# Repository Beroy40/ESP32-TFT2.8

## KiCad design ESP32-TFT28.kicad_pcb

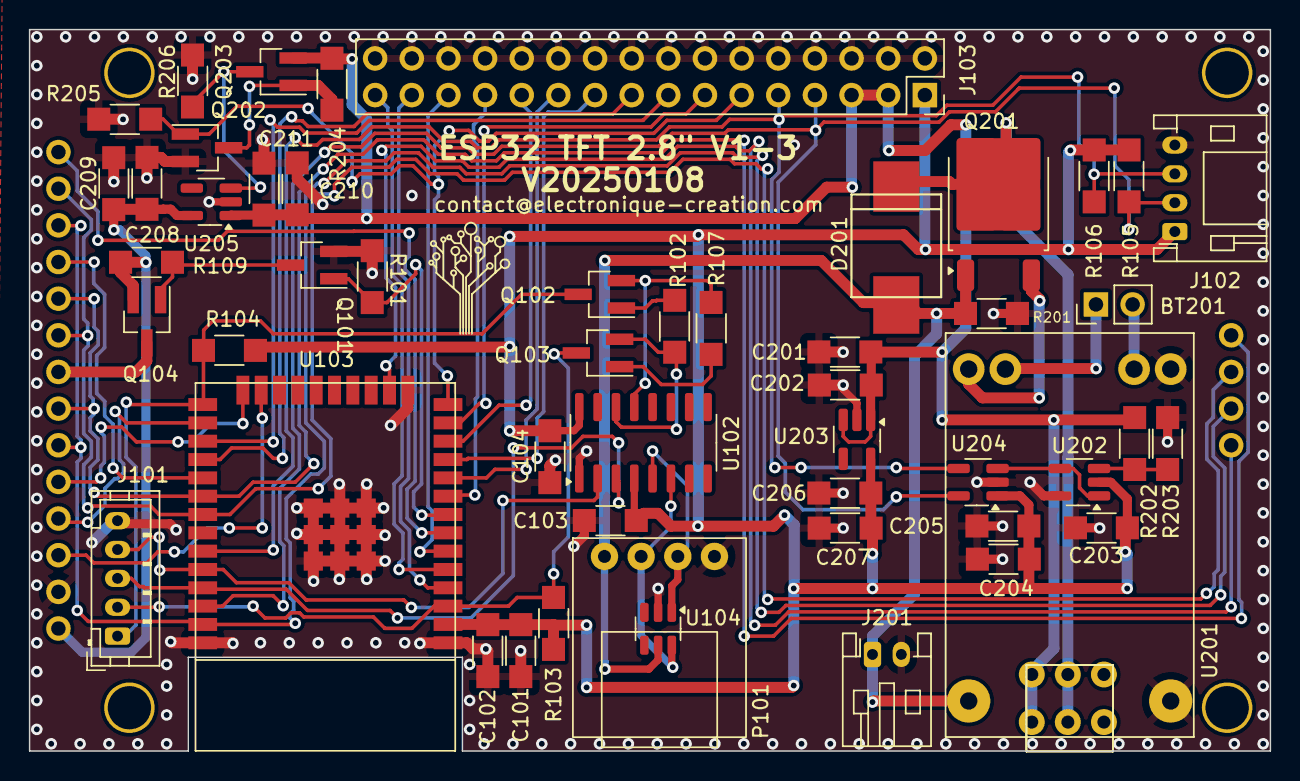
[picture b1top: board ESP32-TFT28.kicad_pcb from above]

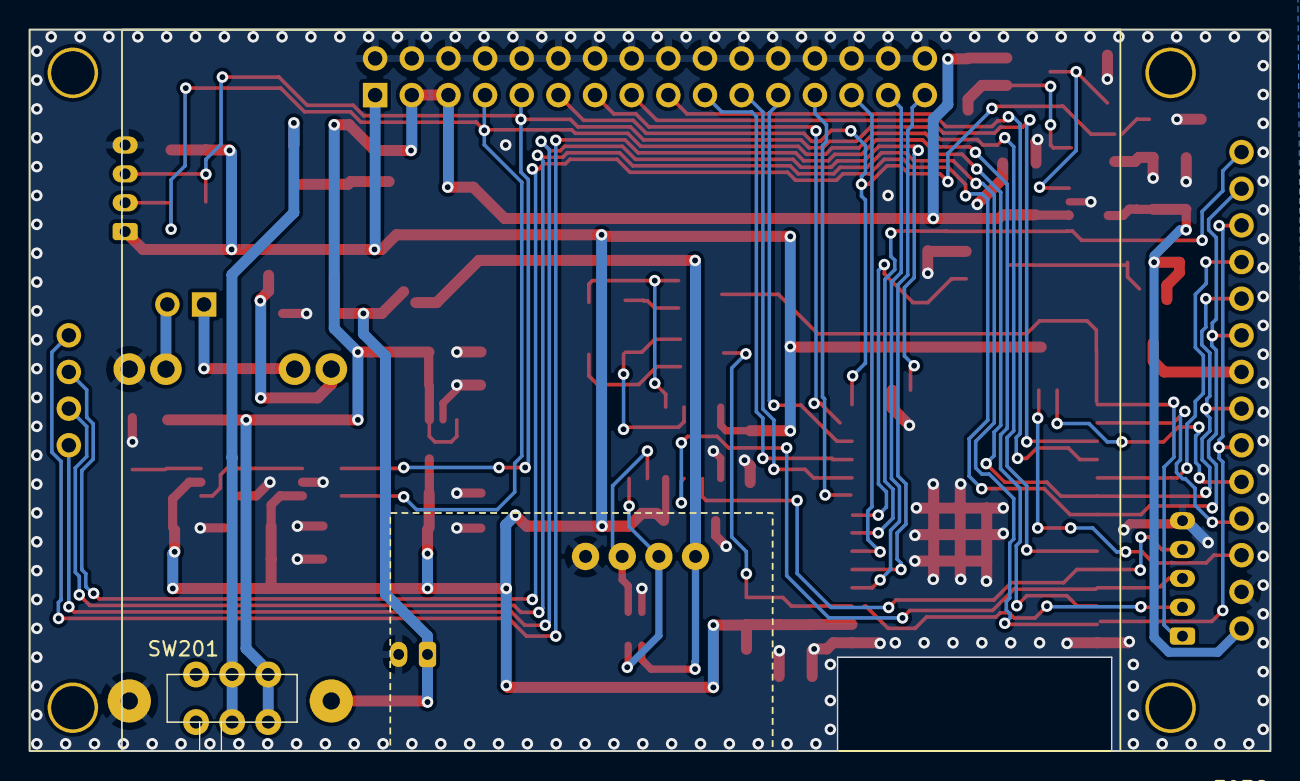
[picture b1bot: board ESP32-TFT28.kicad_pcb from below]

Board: 2 copper layers, 86.0 x 50.0 mm, 54 parts (2 on the bottom side), 48 nets.

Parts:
BT201: Battery_Cell; PinHeader_1x02_P2.54mm_Vertical
C101: CC1206KKX7R7BB106; CMS_1206
C102, C103, C104, C202, C203, C205, C207, C209, C211: 100nF; CMS_1206
C201, C204, C206, C208, C210: 10UF; CMS_1206
D201: SS34; DO-214AB_HANDSOLDERING
J101: B5B-PH-K-S(LF)(SN); JST_PH_B5B-PH-K_1x05_P2.00mm_Vertical
J102: Conn_01x04; JST_PH_S4B-PH-K_1x04_P2.00mm_Horizontal
J103: Conn_02x16_Odd_Even; PinSocket_2x16_P2.54mm_Vertical
J201: CONN_01X02; JST_PH_S2B-PH-K_1x02_P2.00mm_Horizontal
L101: LOGO; PetitLogo
P101: USB_C_Module
Q101, Q202: BSS138; SOT-23_Handsoldering
Q102, Q103: MMBT2222ALT1G; SOT-23_Handsoldering
Q104: Q_PMOS_GSD; SOT-23_Handsoldering
Q201: xxxx; TO-252-2
Q203: DPM1045U; SOT-23_Handsoldering
R101, R103, R104, R109, R201, R204, R205, R206: 10k; CMS_1206
R102, R107: 12k; CMS_1206
R105, R106: 4k7; CMS_1206
R202, R203: R; CMS_1206
SW201: JS202011AQN
U101: TFT_28
U102: CH340C; SOIC-16_3.9x9.9mm_P1.27mm
U103: ESP32_WROOM; ESP32-WROOM-JLCPCB
U104: SRV05-4; SOT-23-6
U201: MODULE_CHARGER_LIPO_WITH_PROTECTION
U202: MCP6001R; SOT-23-5_HandSoldering
U203, U205: RT9080; SOT-23-5_HandSoldering
U204: MCP3221; SOT-23-5_HandSoldering

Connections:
+3V3: C101.1, C102.1, C103.2, C104.2, C203.2, C204.2, C205.2, C206.2, C207.1, J102.1, J103.1, R103.1, R104.1, R105.1, R106.1, U102.4 (V3), U102.16 (VCC), U103.2 (3V3), U202.2 (VDD), U203.5 (Vout), U204.1 (VDD)
+5V: D201.2 (A), J201.1, P101.1 (VBUS), Q201.1 (G), R201.1, U104.5 (VP), U201.1 (IN+)
+BATT: C201.2, C202.1, C210.2, C211.1, J103.3, J103.5, Q203.2 (S), R202.1, R204.2, SW201.3 (C), SW201.6 (C), U203.1 (Vin), U203.3 (EN), U205.1 (Vin)
/BACKLIGHT: Q101.1 (G), R101.1, U103.8 (IO32)
/CLK: U101.7 (SCK), U101.10 (T_CLK), U101.15 (SD_SCK), U103.30 (IO18)
/DTR: Q102.2 (E), R107.2, U102.13 (~DTR)
/EN: J101.2, Q103.3 (C), R103.2, U103.3 (EN)
/EN_VCC: J103.11, Q202.1 (G), R205.2, U103.14 (IO12)
/IO0: J101.1, Q102.3 (C), R104.2, U103.25 (IO0)
/IO14: J103.13, U103.13 (IO14)
/IO16: J103.15, U103.27 (IO16)
/IO17: J103.17, U103.28 (IO17)
/IO25: J103.21, U103.10 (IO25)
/IO26: J103.19, U103.11 (IO26)
/IO27: J103.23, U103.12 (IO27)
/IO33: J103.25, U103.9 (IO33)
/IO34: J103.27, U103.6 (IO34)
/IO36: J103.29, U103.4 (IO36/SENSOR_VP)
/IO39: J103.31, U103.5 (IO39/SENSOR_VN)
/MISO: U101.9 (SDO(MISO)), U101.13 (T_DO), U101.16 (SD_MISO), U103.31 (IO19)
/MOSI: U101.6 (SDI(MOSI)), U101.12 (T_DIN), U101.17 (SD_MOSI), U103.37 (IO23)
/RTS: Q103.2 (E), R102.2, U102.14 (~RTS)
/RX0_ESP: J101.4, U102.2 (TXD), U103.34 (RXD)
/SCL: J102.2, J103.7, R105.2, U103.36 (IO22/SCL), U204.5 (SCL)
/SDA: J102.3, J103.9, R106.2, U103.33 (IO21/SDA), U204.4 (SDA)
/SD_CS: U101.18 (SD_CS), U103.16 (IO13)
/TFT_CS: U101.3 (CS), U103.23 (IO15)
/TFT_DC: U101.5 (D/C), U103.24 (IO2)
/TFT_RST: U101.4 (REST), U103.26 (IO4)
/TOUCH_CS: U101.11 (T_CS), U103.29 (IO5)
/TOUCH_IRQ: U101.14 (T_IRQ), U103.7 (IO35)
/TX0_ESP: J101.3, U102.3 (RXD), U103.35 (TXD)
GND: C101.2, C102.2, C103.1, C104.1, C201.1, C202.2, C203.1, C204.1, C205.1, C206.1, C207.2, C208.1, C209.2, C210.1, C211.2, J101.5, J102.4, J103.2, J103.4, J103.6, J103.8, J103.10, J103.12, J103.14, J103.16, J103.18, J103.20, J103.22, J103.24, J103.26, J103.28, J103.30, J103.32, J201.2, P101.4 (GND), Q101.2 (S), Q202.2 (S), R101.2, R201.2, R203.1, R205.1, R206.2, U101.2 (GND), U102.1 (GND), U103.1 (GND), U103.15 (GND), U103.38 (GND), U103.39 (GND), U104.2 (VN), U201.2 (IN-), U201.3 (OUT-), U202.5 (VSS), U203.2 (GND), U204.2 (VSS), U205.2 (GND)
unnamed: BT201.1 (+), U201.5 (BAT+)
unnamed: BT201.2 (-), U201.4 (BAT-)
unnamed: D201.1 (K), Q201.2 (S), SW201.2 (B), SW201.5 (B)
unnamed: P101.3 (D+), U102.5 (UD+), U104.1 (IO1)
unnamed: P101.2 (D-), U102.6 (UD-), U104.6 (IO4)
unnamed: Q101.3 (D), Q104.1 (G), R109.2
unnamed: Q102.1 (B), R102.1
unnamed: Q103.1 (B), R107.1
unnamed: Q104.3 (D), U101.8 (LED)
unnamed: Q201.3 (D), U201.6 (OUT+)
unnamed: Q202.3 (D), Q203.1 (G), R204.1
unnamed: Q203.3 (D), R206.1, U205.3 (EN)
unnamed: R202.2, R203.2, U202.3 (Vin+)
unnamed: U202.1 (Vout), U202.4 (Vin-), U204.3 (Ain)
VCC: C208.2, C209.1, Q104.2 (S), R109.1, U101.1 (VCC), U205.5 (Vout)

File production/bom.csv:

Designator,Footprint,Quantity,Value,LCSC Part #
BT201,PinHeader_1x02_P2.54mm_Vertical,1,Battery_Cell,
C101,CMS_1206,1,CC1206KKX7R7BB106,
"C102, C103, C104, C202, C203, C205, C207, C209, C211",CMS_1206,9,100nF,
"C201, C204, C206, C208, C210",CMS_1206,5,10UF,
D201,DO-214AB_HANDSOLDERING,1,SS34,
J101,JST_PH_B5B-PH-K_1x05_P2.00mm_Vertical,1,B5B-PH-K-S(LF)(SN),
J102,JST_PH_S4B-PH-K_1x04_P2.00mm_Horizontal,1,Conn_01x04,
J103,PinSocket_2x16_P2.54mm_Vertical,1,Conn_02x16_Odd_Even,
J201,JST_PH_S2B-PH-K_1x02_P2.00mm_Horizontal,1,CONN_01X02,
L101,PetitLogo,1,LOGO,
P101,USB_C_Module,1,USB_C_Module,
"Q101, Q202",SOT-23_Handsoldering,2,BSS138,
"Q102, Q103",SOT-23_Handsoldering,2,MMBT2222ALT1G,
Q201,TO-252-2,1,DMP1045U,
"R101, R103, R104, R201, R204, R205",CMS_1206,6,10k,
"R102, R107",CMS_1206,2,12k,
"R105, R106",CMS_1206,2,4k7,
R108,CMS_1206,1,0R,
"R202, R203",CMS_1206,2,R,
U101,TFT_28,1,~,
U102,SOIC-16_3.9x9.9mm_P1.27mm,1,CH340C,
U103,ESP32-WROOM-JLCPCB,1,ESP32_WROOM,
U201,MODULE_CHARGER_LIPO_WITH_PROTECTION,1,MODULE_CHARGER_LIPO_WITH_PROTECTION,
U202,SOT-23-5_HandSoldering,1,MCP6001R,
"U203, U205",SOT-23-5_HandSoldering,2,RT9080,
U204,SOT-23-5_HandSoldering,1,MCP3221,

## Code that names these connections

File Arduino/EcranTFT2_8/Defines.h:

#ifndef DEFINES_H
#define DEFINES_H

//#include <Adafruit_MCP23X17.h>

#define MOSI  23
#define MISO  19
#define CLK 18

#define TOUCH_IRQ 35
#define TOUCH_CS  5
#define TFT_RST 4
#define TFT_DC  2
#define TFT_CS  15
#define SD_CS 13
#define TFT_BL  32
#define BL_ON  digitalWrite(TFT_BL,HIGH)
#define BL_OFF  digitalWrite(TFT_BL,LOW)
#define EN_VCC  12
#define VCC_ON  digitalWrite(EN_VCC,LOW)
#define VCC_OFF  digitalWrite(EN_VCC,HIGH)
#define I2C_SDA 21
#define I2C_SCL 22

#define FREQ_I2C  400000

#define TIME_SURVEILLANCE_BATTERIE  5000

#define DECLINAISON_MAGNETIQUE  3.5


#endif

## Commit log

2025-01-12 first commit Kicad
